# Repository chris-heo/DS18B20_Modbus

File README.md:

# Modbus adapter for DS18B20 temperature sensors (and more)

Quick facts:
* 7 channels for DS18B20 (and compatible devices)
* 1 ADC channel
* 8 pulse counters
* I2C interface for AMS AS5600 magnetic encoder
* Modbus RTU
* ATtiny1616

[Documentation](https://hobbyelektronik.org/w/index.php/DS18B20-Modbus-Adapter) (German)

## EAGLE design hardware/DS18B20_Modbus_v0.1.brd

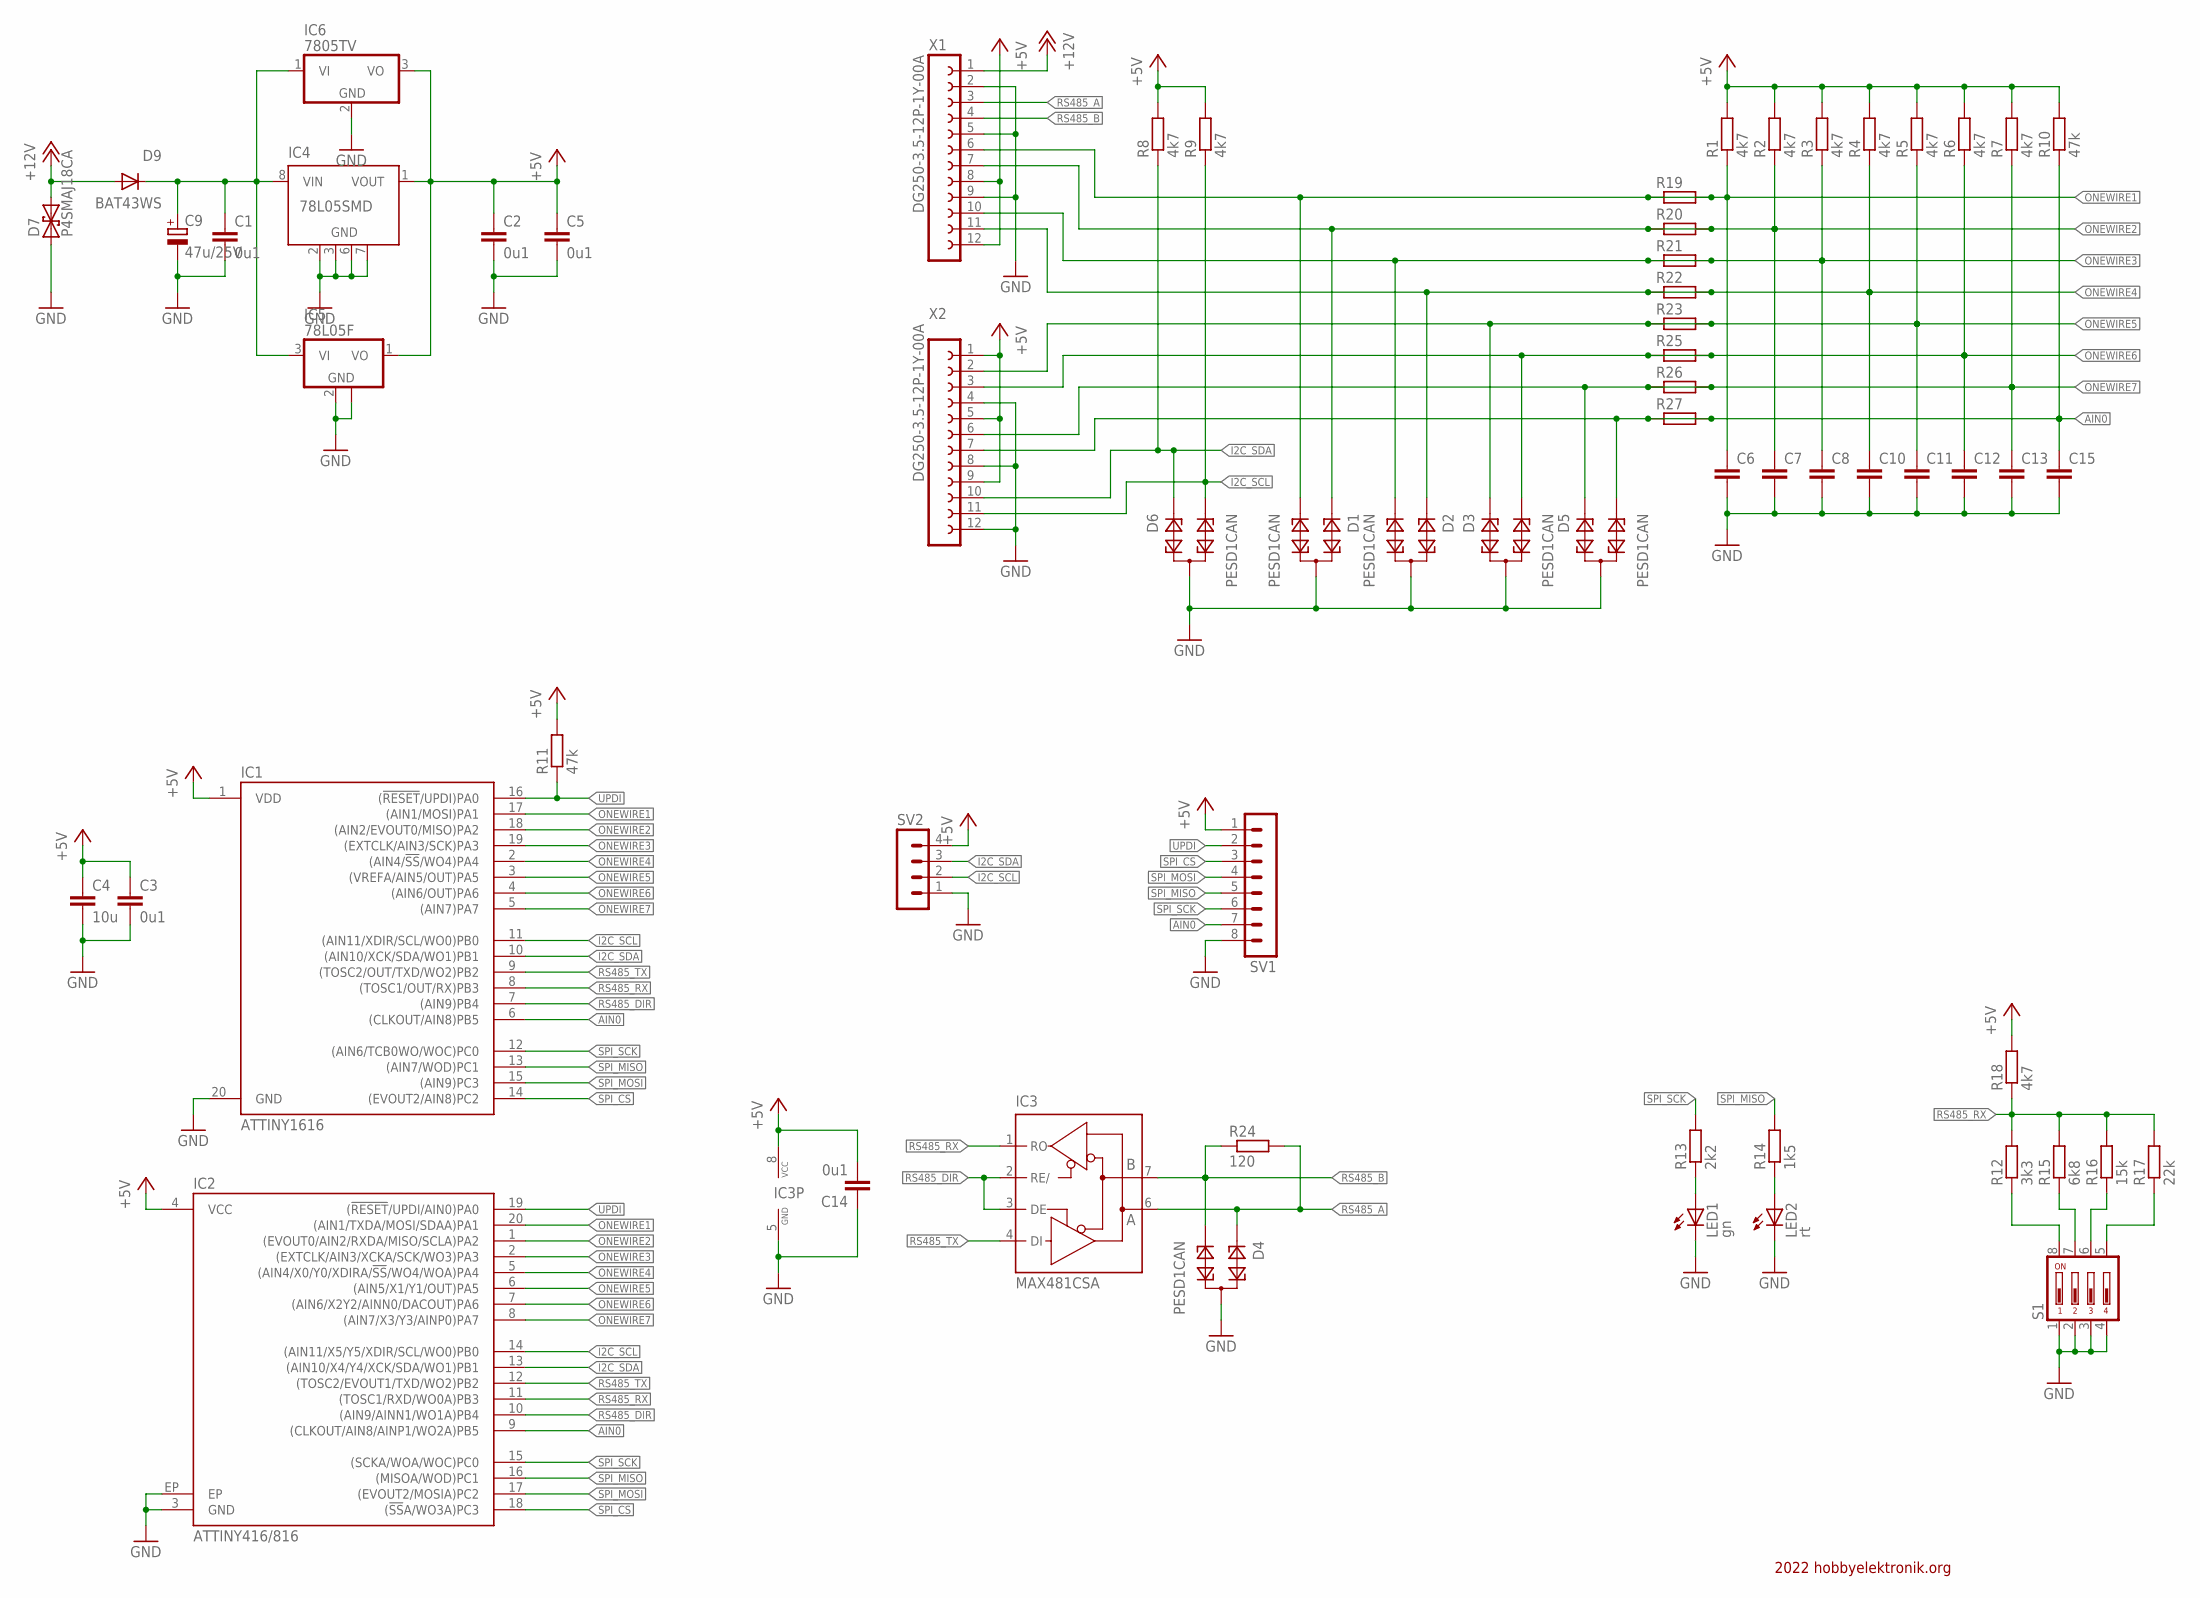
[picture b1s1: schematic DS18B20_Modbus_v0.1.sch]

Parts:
C1: 0u1; C0805
C2, C3, C5, C14: 0u1; C0603
C4: 10u; C0805
C6, C7, C8, C10, C11, C12, C13, C15: C-EUC0603; C0603
C9: 47u/25V; E2,5-5
D1, D2, D3, D4, D5, D6: PESD1CAN; SOT23
D7: P4SMAJ18CA; DO214AC
D9: BAT43WS; SOD323-W
IC1: ATTINY1616; SO20_T1616
IC2: ATTINY416/816; ZCL_VQFN-20
IC3: MAX481CSA; SO08
IC4: 78L05SMD; SO08
IC5: 78L05F; SOT89
IC6: 7805TV; TO220V
LED1: gn; SML0805
LED2: rt; SML0805
R1, R2, R3, R4, R5, R6, R7, R8, R9, R18: 4k7; R0603
R10, R11: 47k; R0603
R12: 3k3; R0603
R13: 2k2; R0603
R14: 1k5; R0603
R15: 6k8; R0603
R16: 15k; R0603
R17: 22k; R0603
R19, R20, R21, R22, R23, R25, R26, R27: R-EU_R0603; R0603
R24: 120; R0603
S1: DS04; DS-04
SV1: MA08-1R
SV2: MA04-1R
X1, X2: DG250-3.5-12P-1Y-00A

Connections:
+5V: C2.1, C3.1, C4.1, C5.1, C14.2, IC1.1 (VDD), IC2.4 (VCC), IC3.8 (VCC), IC4.1 (VOUT), IC5.1 (VO), IC6.3 (VO), R1.2, R2.2, R3.2, R4.2, R5.2, R6.2, R7.2, R8.2, R9.2, R10.2, R11.2, R18.2, SV1.1, SV2.4, X1.8, X1.12, X2.1, X2.5, X2.9
+12V: D7.2, D9.A, X1.1
AIN0: C15.1, D5.2, IC1.6 ((CLKOUT/AIN8)PB5), IC2.9 ((CLKOUT/AIN8/AINP1/WO2A)PB5), R10.1, R27.1, R27.2, SV1.7, X2.7
GND: C1.2, C2.2, C3.2, C4.2, C5.2, C6.2, C7.2, C8.2, C9.-, C10.2, C11.2, C12.2, C13.2, C14.1, C15.2, D1.3, D2.3, D3.3, D4.3, D5.3, D6.3, D7.1, IC1.20 (GND), IC2.3 (GND), IC2.EP, IC3.5 (GND), IC4.2 (GND), IC4.3 (GND), IC4.6 (GND), IC4.7 (GND), IC5.2 (GND), IC5.2@1 (GND), IC6.2 (GND), LED1.C, LED2.C, S1.1, S1.2, S1.3, S1.4, SV1.8, SV2.1, X1.2, X1.5, X1.9, X2.4, X2.8, X2.12
I2C_SCL: D6.2, IC1.11 ((AIN11/XDIR/SCL/WO0)PB0), IC2.14 ((AIN11/X5/Y5/XDIR/SCL/WO0)PB0), R9.1, SV2.2, X2.11
I2C_SDA: D6.1, IC1.10 ((AIN10/XCK/SDA/WO1)PB1), IC2.13 ((AIN10/X4/Y4/XCK/SDA/WO1)PB1), R8.1, SV2.3, X2.10
unnamed: R12.1, S1.8
unnamed: R15.1, S1.7
unnamed: R16.1, S1.6
unnamed: R17.1, S1.5
unnamed: LED1.A, R13.1
unnamed: LED2.A, R14.1
unnamed: C1.1, C9.+, D9.C, IC4.8 (VIN), IC5.3 (VI), IC6.1 (VI)
ONEWIRE1: C6.1, D1.2, IC1.17 ((AIN1/MOSI)PA1), IC2.20 ((AIN1/TXDA/MOSI/SDAA)PA1), R1.1, R19.1, R19.2, X1.6
ONEWIRE2: C7.1, D1.1, IC1.18 ((AIN2/EVOUT0/MISO)PA2), IC2.1 ((EVOUT0/AIN2/RXDA/MISO/SCLA)PA2), R2.1, R20.1, R20.2, X1.7
ONEWIRE3: C8.1, D2.2, IC1.19 ((EXTCLK/AIN3/SCK)PA3), IC2.2 ((EXTCLK/AIN3/XCKA/SCK/WO3)PA3), R3.1, R21.1, R21.2, X1.10
ONEWIRE4: C10.1, D2.1, IC1.2 ((AIN4/!SS!/WO4)PA4), IC2.5 ((AIN4/X0/Y0/XDIRA/!SS!/WO4/WOA)PA4), R4.1, R22.1, R22.2, X1.11
ONEWIRE5: C11.1, D3.1, IC1.3 ((VREFA/AIN5/OUT)PA5), IC2.6 ((AIN5/X1/Y1/OUT)PA5), R5.1, R23.1, R23.2, X2.2
ONEWIRE6: C12.1, D3.2, IC1.4 ((AIN6/OUT)PA6), IC2.7 ((AIN6/X2Y2/AINN0/DACOUT)PA6), R6.1, R25.1, R25.2, X2.3
ONEWIRE7: C13.1, D5.1, IC1.5 ((AIN7)PA7), IC2.8 ((AIN7/X3/Y3/AINP0)PA7), R7.1, R26.1, R26.2, X2.6
RS485_A: D4.1, IC3.6 (A), R24.2, X1.3
RS485_B: D4.2, IC3.7 (B), R24.1, X1.4
RS485_DIR: IC1.7 ((AIN9)PB4), IC2.10 ((AIN9/AINN1/WO1A)PB4), IC3.2 (RE/), IC3.3 (DE)
RS485_RX: IC1.8 ((TOSC1/OUT/RX)PB3), IC2.11 ((TOSC1/RXD/WO0A)PB3), IC3.1 (RO), R12.2, R15.2, R16.2, R17.2, R18.1
RS485_TX: IC1.9 ((TOSC2/OUT/TXD/WO2)PB2), IC2.12 ((TOSC2/EVOUT1/TXD/WO2)PB2), IC3.4 (DI)
SPI_CS: IC1.14 ((EVOUT2/AIN8)PC2), IC2.18 ((!SS!A/WO3A)PC3), SV1.3
SPI_MISO: IC1.13 ((AIN7/WOD)PC1), IC2.16 ((MISOA/WOD)PC1), R14.2, SV1.5
SPI_MOSI: IC1.15 ((AIN9)PC3), IC2.17 ((EVOUT2/MOSIA)PC2), SV1.4
SPI_SCK: IC1.12 ((AIN6/TCB0WO/WOC)PC0), IC2.15 ((SCKA/WOA/WOC)PC0), R13.2, SV1.6
UPDI: IC1.16 ((!RESET!/UPDI)PA0), IC2.19 ((!RESET!/UPDI/AIN0)PA0), R11.1, SV1.2

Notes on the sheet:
2022 hobbyelektronik.org

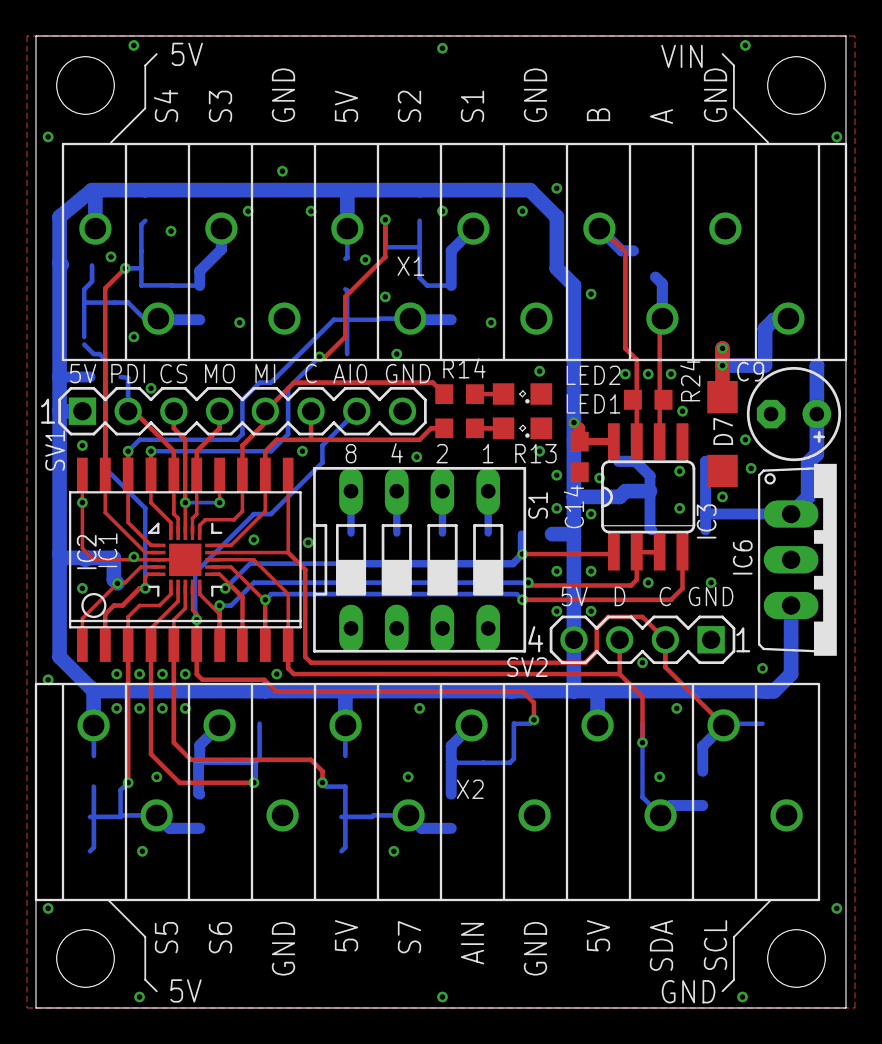
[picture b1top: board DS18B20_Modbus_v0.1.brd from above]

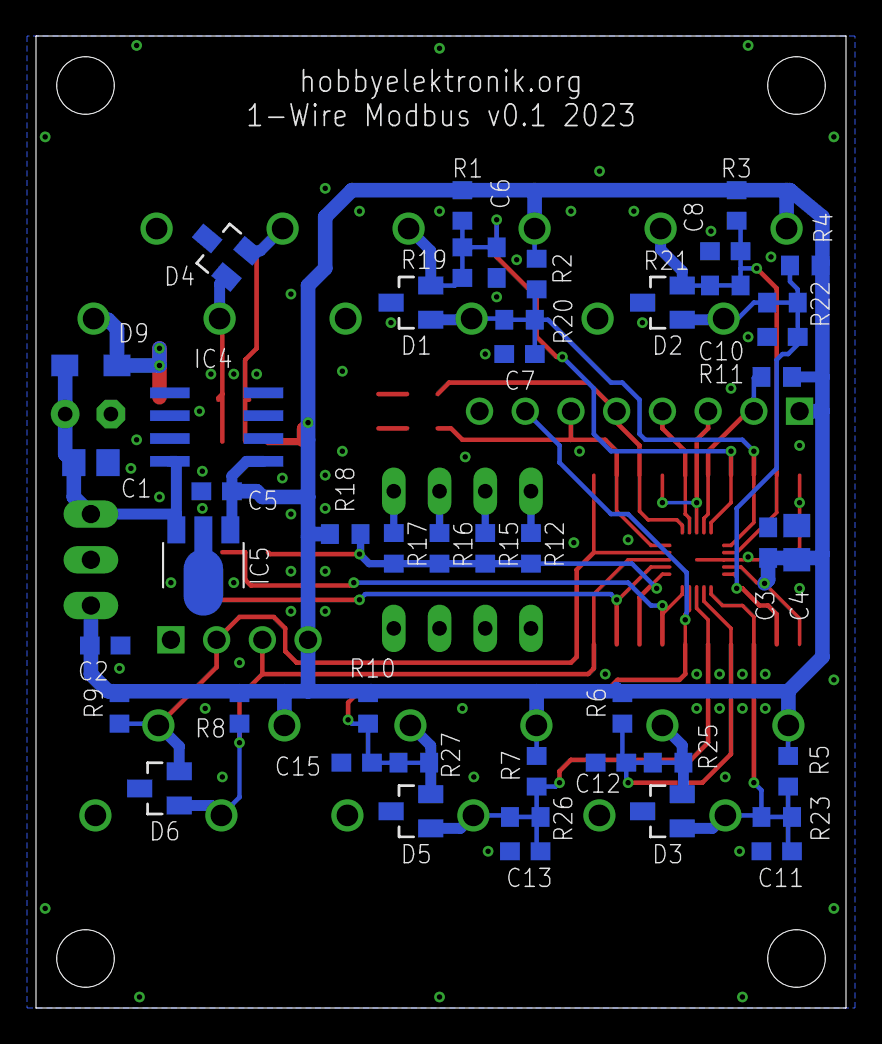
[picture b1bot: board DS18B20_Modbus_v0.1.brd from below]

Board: 2 copper layers, 45.0 x 54.0 mm, 63 parts (46 on the bottom side), 30 nets.

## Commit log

2024-01-17 initial release
